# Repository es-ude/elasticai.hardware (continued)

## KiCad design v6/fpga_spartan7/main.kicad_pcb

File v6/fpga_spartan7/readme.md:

# ENv6 FPGA Board: AMD Spartan-7

FPGA board for the ENv6 base board with an AMD Spartan-7. Intended FPGA board IDs: **7** (S15, 10 kΩ) and **8** (S50, 15 kΩ).

## Contents (KiCad sheets)

- `FPGA_Power_Config`: power supply (REF3012 reference) and configuration (S25FL256S flash)
- `FPGA_IO_Banks`: IO banks, 100 MHz oscillator
- `Connectors`: ENv6 connector (base board and application board)

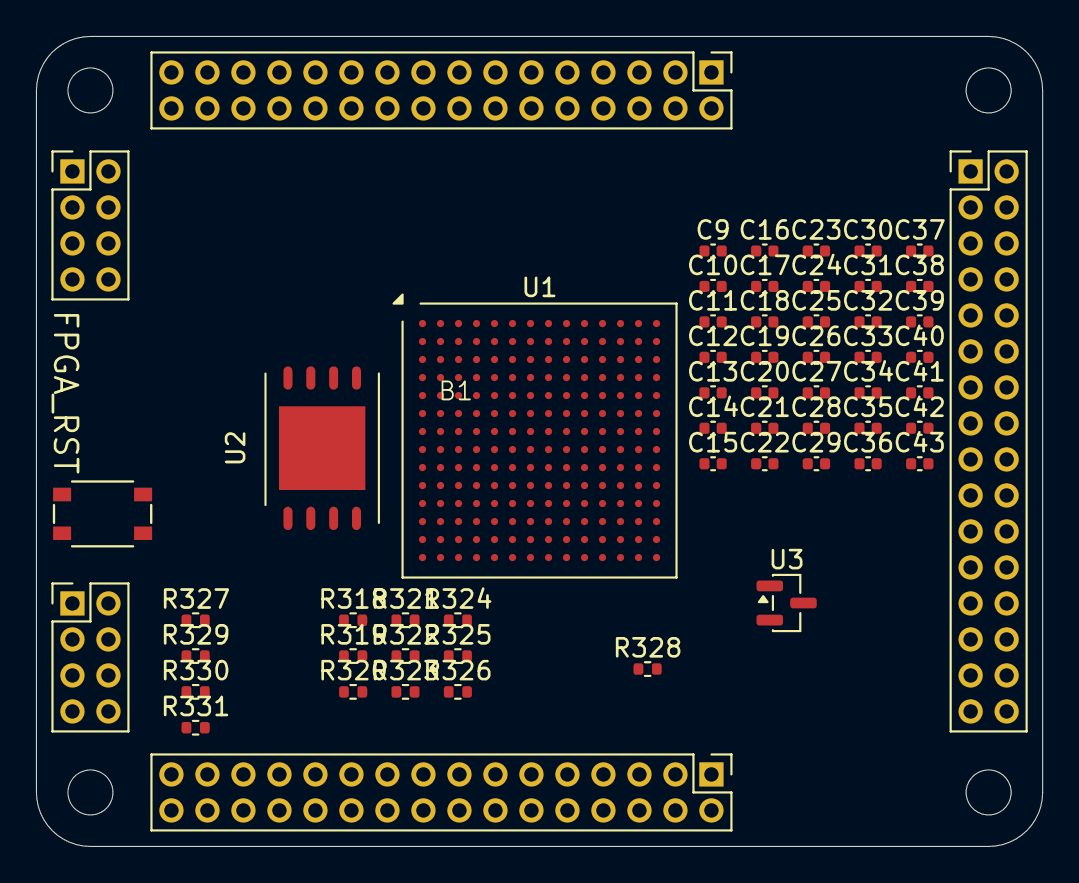
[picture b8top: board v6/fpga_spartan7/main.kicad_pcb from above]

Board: 2 copper layers, 55.9 x 45.0 mm, 54 parts (0 on the bottom side), 50 nets, no tracks yet.

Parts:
B1: ExtensionBoard_ENv6
C9, C10, C11, C12, C13, C14, C15, C19, C20, C21, C22, C23, C24, C25, C26, C27, C30, C31, C32, C33, C34, C37, C38, C39, C40, C41: 10u; C_0402_1005Metric
C16, C17, C18, C28, C29, C35, C36, C42, C43: 1u; C_0402_1005Metric
R318, R319, R320, R321: 100R; R_0402_1005Metric
R322, R323, R324, R325, R327: 2kR; R_0402_1005Metric
R326: 4.7kR; R_0402_1005Metric
R328: TBD; R_0402_1005Metric
R329, R330, R331: 0R; R_0402_1005Metric
S401: FPGA_RST; TACTILE-SWITCH
U1: AMD Spartan S7; BGA_FTGB196
U2: S25FL256S; WSON-8_EP_8x6_Pitch1.27mm
U3: REF3012; SOT-23

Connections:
1V0: B1.C3, B1.C4, B1.C5, B1.C6, B1.C7, B1.C8
1V8: B1.C11, B1.C12, B1.C13, B1.C14, B1.C15, B1.C16
3V3: B1.C19, B1.C20, B1.C21, B1.C22, B1.C23, B1.C24
/FPGA_Power_Config/XADC_VREF: U1.H8 (VREFP_0), U3.2 (OUT)
ADC_Detect2: B1.B17, R328.2
FLASH_CS: R326.2, U1.C11 (IO_L6P_T0_FCS_B_14), U2.1 (~CS)
FLASH_IO2: R320.2, R324.2, U2.3 (~WP/IO2)
FLASH_IO3: R321.2, R325.2, U2.7 (~HOLD/IO3)
FLASH_MISO: R319.2, R323.2, U2.2 (SO/IO1)
FLASH_MOSI: R318.2, R322.2, U2.5 (SI/IO0)
FPGA_1V: C9.2, C10.2, C11.2, C12.2, C13.2, C14.2, C15.2, C16.2, C17.2, C18.2, C19.2, C20.2, C21.2, C22.2, C37.2, C38.2, C39.2, C40.2, C41.2, C42.2, C43.2, U1.D6 (VCCINT), U1.D8 (VCCINT), U1.E5 (VCCBRAM), U1.E7 (VCCINT), U1.E9 (VCCINT), U1.F6 (VCCINT), U1.G5 (VCCBRAM), U1.G9 (VCCINT), U1.H6 (VCCINT), U1.J5 (VCCBRAM), U1.J9 (VCCINT), U1.K6 (VCCINT), U1.K8 (VCCINT)
FPGA_1V8: C23.2, C24.2, C25.2, C26.2, C27.2, C28.2, C29.2, R329.2, R330.2, U1.F10 (VCCAUX), U1.H10 (VCCAUX), U1.K10 (VCCAUX), U1.L9 (VCCAUX)
FPGA_3V3: C30.2, C31.2, C32.2, C33.2, C34.2, C35.2, C36.2, R322.1, R323.1, R324.1, R325.1, R326.1, R327.2, U1.G2 (VCCO_34), U1.G13 (VCCO_14), U1.K2 (VCCO_34), U1.K13 (VCCO_14), U1.N2 (VCCO_34), U1.N6 (VCCO_0), U1.N8 (VCCO_0), U1.N13 (VCCO_14), U2.8 (VCC), U3.1 (IN)
FPGA_CCLK: U1.A8 (CCLK_0), U2.6 (SCK)
FPGA_DONE: B1.A23, U1.P9 (DONE_0)
FPGA_INIT: B1.A25, U1.P8 (INIT_B_0)
FPGA_IO_0: B1.A5, U1.A12 (IO_L4P_T0_D04_14)
FPGA_IO_1: B1.A6, U1.A13 (IO_L4N_T0_D05_14)
FPGA_IO_2: B1.A7, U1.B13 (IO_L5P_T0_D06_14)
FPGA_IO_3: B1.A8, U1.B14 (IO_L5N_T0_D07_14)
FPGA_IO_4: B1.A9, U1.C12 (IO_L6N_T0_D08_VREF_14)
FPGA_IO_5: B1.A10, U1.F12 (IO_L7P_T1_D09_14)
FPGA_IO_6: B1.A11, U1.E12 (IO_L7N_T1_D10_14)
FPGA_IO_7: B1.A12, U1.D12 (IO_L8P_T1_D11_14)
FPGA_IO_A_0: B1.B30, U1.P11 (IO_L24N_T3_D16_14)
FPGA_IO_A_1: B1.B29, U1.P10 (IO_L24P_T3_D17_14)
FPGA_IO_A_2: B1.B28, U1.N11 (IO_L23N_T3_D18_14)
FPGA_IO_A_3: B1.B27, U1.N10 (IO_L23P_T3_D19_14)
FPGA_IO_A_4: B1.B26, U1.P13 (IO_L22N_T3_D20_14)
FPGA_IO_A_5: B1.B25, U1.P12 (IO_L22P_T3_D21_14)
FPGA_IO_A_6: B1.B24, U1.M14 (IO_L21N_T3_DQS_D22_14)
FPGA_IO_A_7: B1.B23, U1.M12 (IO_L20N_T3_D23_14)
FPGA_M0: B1.A28, U1.M7 (M0_0)
FPGA_M1: B1.A27, U1.M8 (M1_0)
FPGA_M2: B1.A29, U1.M9 (M2_0)
FPGA_RESET: B1.A26, R327.1, S401.1, S401.2 (1), U1.L7 (PROGRAM_B_0)
GND: B1.A3, B1.A4, B1.A13, B1.A14, B1.A31, B1.A32, B1.B9, B1.B10, B1.B20, B1.B22, B1.B31, B1.B32, B1.C1, B1.C2, B1.C9, B1.C10, B1.C17, B1.C18, B1.C25, B1.C26, B1.D1, B1.D2, B1.D3, B1.D4, B1.D5, B1.D6, B1.D7, B1.D8, B1.E1, B1.E2, B1.E3, B1.E4, B1.E5, B1.E6, B1.E7, B1.E8, C9.1, C10.1, C11.1, C12.1, C13.1, C14.1, C15.1, C16.1, C17.1, C18.1, C19.1, C20.1, C21.1, C22.1, C23.1, C24.1, C25.1, C26.1, C27.1, C28.1, C29.1, C30.1, C31.1, C32.1, C33.1, C34.1, C35.1, C36.1, C37.1, C38.1, C39.1, C40.1, C41.1, C42.1, C43.1, S401.3 (2), S401.4 (2), U1.A1 (GND), U1.A6 (GND), U1.A9 (GND), U1.A11 (GND), U1.A14 (GND), U1.B4 (GND), U1.B7 (GND), U1.B9 (GND), U1.C2 (GND), U1.C6 (GND), U1.C7 (GND), U1.C8 (GND), U1.C9 (GND), U1.C13 (GND), U1.D5 (GND), U1.D7 (GND), U1.D9 (GND), U1.D11 (GND), U1.E1 (GND), U1.E3 (GND), U1.E6 (GND), U1.E8 (GND), U1.E10 (GND), U1.E14 (GND), U1.F5 (GND), U1.F7 (GNDADC_0), U1.F9 (GND), U1.G3 (GND), U1.G6 (GND), U1.G7 (VREFN_0), U1.G10 (GND), U1.G12 (GND), U1.H5 (GND), U1.H9 (GND), U1.J6 (GND), U1.J7 (DXN_0), U1.J8 (DXP_0), U1.J10 (GND), U1.K1 (GND), U1.K5 (GND), U1.K7 (GND), U1.K9 (GND), U1.K14 (GND), U1.L4 (GND), U1.L6 (GND), U1.L8 (GND), U1.L10 (GND), U1.L11 (GND), U1.N3 (GND), U1.N5 (GND), U1.N9 (GND), U1.N12 (GND), U1.P1 (GND), U1.P14 (GND), U2.4 (VSS), U2.9 (VSS), U3.3 (GND)
JTAG_TCK_GP18: B1.A21, U1.A7 (TCK_0)
JTAG_TDI_GP16: B1.A19, U1.P7 (TDI_0)
JTAG_TDO_GP17: B1.A22, U1.P6 (TDO_0)
JTAG_TMS_GP19: B1.A24, U1.M6 (TMS_0)
unnamed: R319.1, U1.B12 (IO_L1N_T0_D01_DIN_14)
unnamed: R318.1, U1.B11 (IO_L1P_T0_D00_MOSI_14)
unnamed: R321.1, U1.C10 (IO_L2N_T0_D03_14)
unnamed: R320.1, U1.D10 (IO_L2P_T0_D02_14)
unnamed: R331.1, U1.N7 (CFGBVS_0)
unnamed: R330.1, U1.F8 (VCCADC_0)
unnamed: R329.1, U1.B8 (VCCBAT)
OSC_100: U1.A10 (IO_L3N_T0_DQS_EMCCLK_14), U1.H11 (IO_L13P_T2_MRCC_14)
VMCU: B1.A30, B1.B21, R328.1
